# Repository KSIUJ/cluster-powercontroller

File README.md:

# cluster-powercontroller
AVR-based node power controller for the KSI computer cluster

* 32 opto-isolated channels
* Atmel ATMega328P
* USB interface via FT232R

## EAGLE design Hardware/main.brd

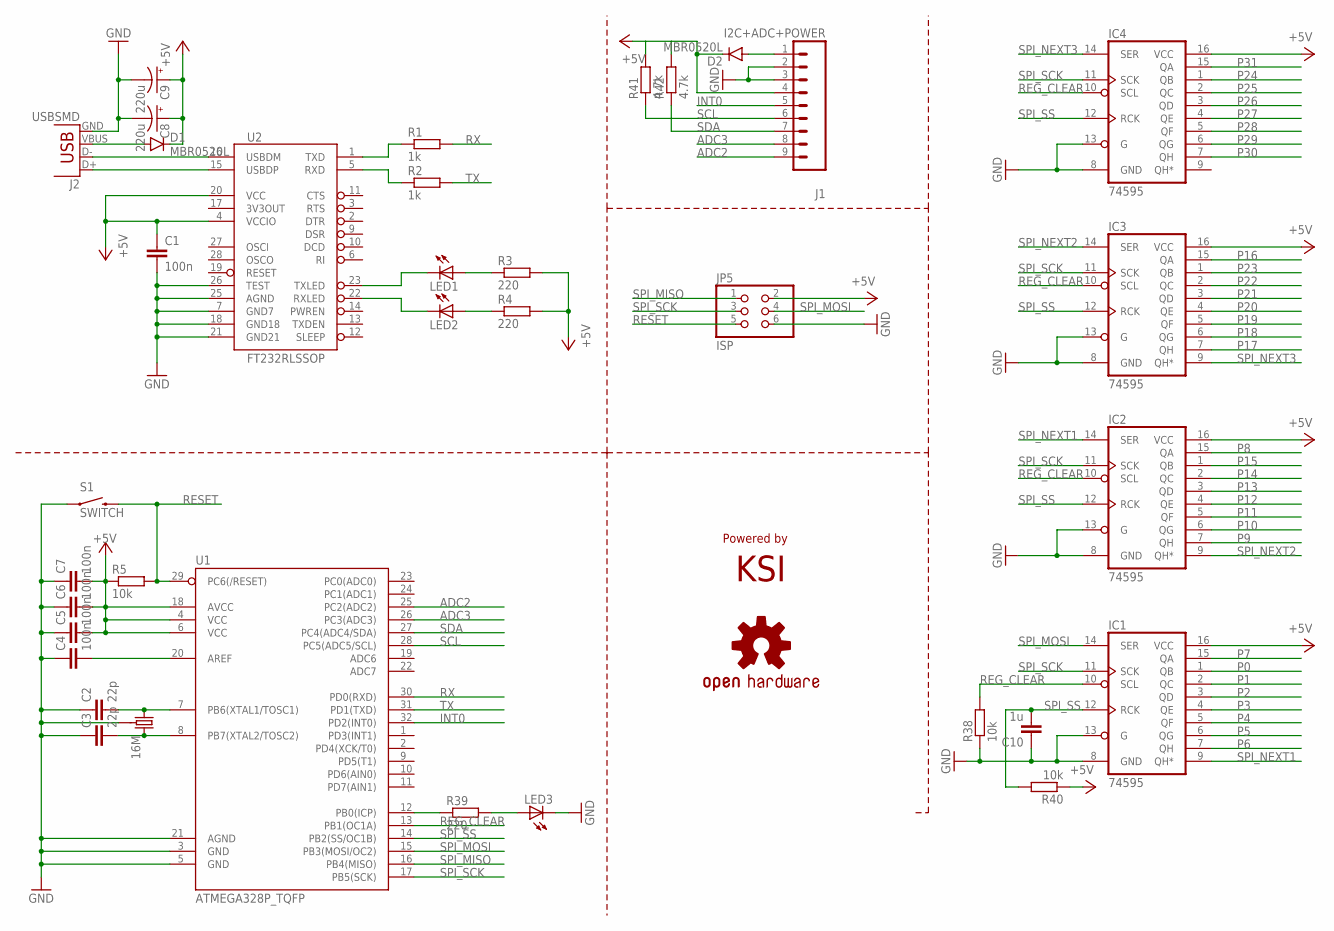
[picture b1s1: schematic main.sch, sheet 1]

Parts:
C1, C4, C5, C6, C7: 100n; C0805
C2, C3: 22p; C0805
C8, C9: 220u; EIA7343
C10: 1u; C0805
D1, D2: MBR0520L; SOD-123
IC1, IC2, IC3, IC4: 74595; TSSOP16
J1: I2C+ADC+POWER; 1X09
J2: USBSMD; USB-MINIB
JP5: ISP; 2X03
LED1, LED2, LED3: LEDSML0805; SML0805
LOGO1: OSHW-LOGOM; OSHW-LOGO-M
R1, R2: 1k; R0805
R3, R4, R39: 220; R0805
R5, R38, R40: 10k; R0805
R41, R42: 4.7k; R0805
S1: SWITCH; TACTILE_SWITCH_TALL
U1: ATMEGA328P_TQFP; TQFP32-08
U2: FT232RLSSOP; SSOP28DB
U$17: KSI; KSI_LOGO
Y2: 16M; CRYSTAL-SMD-5X3

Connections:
+5V: C1.1, C5.2, C6.2, C7.2, C8.A (+), C9.A (+), D1.C, D2.C, IC1.16 (VCC), IC2.16 (VCC), IC3.16 (VCC), IC4.16 (VCC), J1.4, JP5.2, R3.2, R4.2, R5.1, R40.1, R41.2, R42.2, U1.4 (VCC), U1.6 (VCC), U1.18 (AVCC), U2.4 (VCCIO), U2.20 (VCC); also elsewhere on the board
ADC2: J1.9, U1.25 (PC2(ADC2))
ADC3: J1.8, U1.26 (PC3(ADC3))
GND: C1.2, C2.1, C3.1, C4.1, C5.1, C6.1, C7.1, C8.C (-), C9.C (-), C10.1, IC1.8 (GND), IC1.13 (G), IC2.8 (GND), IC2.13 (G), IC3.8 (GND), IC3.13 (G), IC4.8 (GND), IC4.13 (G), J1.2, J1.3, J2.GND, JP5.6, LED3.C, R38.1, S1.A2 (1), U1.3 (GND), U1.5 (GND), U1.21 (AGND), U2.7 (GND7), U2.18 (GND18), U2.21 (GND21), U2.25 (AGND), U2.26 (TEST), Y2.2 (3), Y2.4 (3)
INT0: J1.5, U1.32 (PD2(INT0))
unnamed: J2.D-, U2.16 (USBDM)
unnamed: J2.D+, U2.15 (USBDP)
unnamed: R1.1, U2.1 (TXD)
unnamed: R2.1, U2.5 (RXD)
unnamed: LED1.A, R3.1
unnamed: LED2.A, R4.1
unnamed: LED1.C, U2.23 (TXLED)
unnamed: LED2.C, U2.22 (RXLED)
unnamed: C2.2, U1.7 (PB6(XTAL1/TOSC1)), Y2.3 (1)
unnamed: C3.2, U1.8 (PB7(XTAL2/TOSC2)), Y2.1 (2)
unnamed: C4.2, U1.20 (AREF)
unnamed: R39.1, U1.12 (PB0(ICP))
unnamed: LED3.A, R39.2
unnamed: D1.A, J2.VBUS
unnamed: D2.A, J1.1
P0: IC1.1 (QB); also elsewhere on the board
P1: IC1.2 (QC); also elsewhere on the board
P2: IC1.3 (QD); also elsewhere on the board
P3: IC1.4 (QE); also elsewhere on the board
P4: IC1.5 (QF); also elsewhere on the board
P5: IC1.6 (QG); also elsewhere on the board
P6: IC1.7 (QH); also elsewhere on the board
P7: IC1.15 (QA); also elsewhere on the board
P8: IC2.15 (QA); also elsewhere on the board
P9: IC2.7 (QH); also elsewhere on the board
P10: IC2.6 (QG); also elsewhere on the board
P11: IC2.5 (QF); also elsewhere on the board
P12: IC2.4 (QE); also elsewhere on the board
P13: IC2.3 (QD); also elsewhere on the board
P14: IC2.2 (QC); also elsewhere on the board
P15: IC2.1 (QB); also elsewhere on the board
P16: IC3.15 (QA); also elsewhere on the board
P17: IC3.7 (QH); also elsewhere on the board
P18: IC3.6 (QG); also elsewhere on the board
P19: IC3.5 (QF); also elsewhere on the board
P20: IC3.4 (QE); also elsewhere on the board
P21: IC3.3 (QD); also elsewhere on the board
P22: IC3.2 (QC); also elsewhere on the board
P23: IC3.1 (QB); also elsewhere on the board
P24: IC4.1 (QB); also elsewhere on the board
P25: IC4.2 (QC); also elsewhere on the board
P26: IC4.3 (QD); also elsewhere on the board
P27: IC4.4 (QE); also elsewhere on the board
P28: IC4.5 (QF); also elsewhere on the board
P29: IC4.6 (QG); also elsewhere on the board
P30: IC4.7 (QH); also elsewhere on the board
P31: IC4.15 (QA); also elsewhere on the board
REG_CLEAR: IC1.10 (SCL), IC2.10 (SCL), IC3.10 (SCL), IC4.10 (SCL), R38.2, U1.13 (PB1(OC1A))
RESET: JP5.5, R5.2, S1.B2 (2), U1.29 (PC6(/RESET))
RX: R1.2, U1.30 (PD0(RXD))
SCL: J1.6, R41.1, U1.28 (PC5(ADC5/SCL))
SDA: J1.7, R42.1, U1.27 (PC4(ADC4/SDA))
SPI_MISO: JP5.1, U1.16 (PB4(MISO))
SPI_MOSI: IC1.14 (SER), JP5.4, U1.15 (PB3(MOSI/OC2))
SPI_NEXT1: IC1.9 (QH*), IC2.14 (SER)
SPI_NEXT2: IC2.9 (QH*), IC3.14 (SER)
SPI_NEXT3: IC3.9 (QH*), IC4.14 (SER)
SPI_SCK: IC1.11 (SCK), IC2.11 (SCK), IC3.11 (SCK), IC4.11 (SCK), JP5.3, U1.17 (PB5(SCK))
SPI_SS: C10.2, IC1.12 (RCK), IC2.12 (RCK), IC3.12 (RCK), IC4.12 (RCK), R40.2, U1.14 (PB2(SS/OC1B))
TX: R2.2, U1.31 (PD1(TXD))

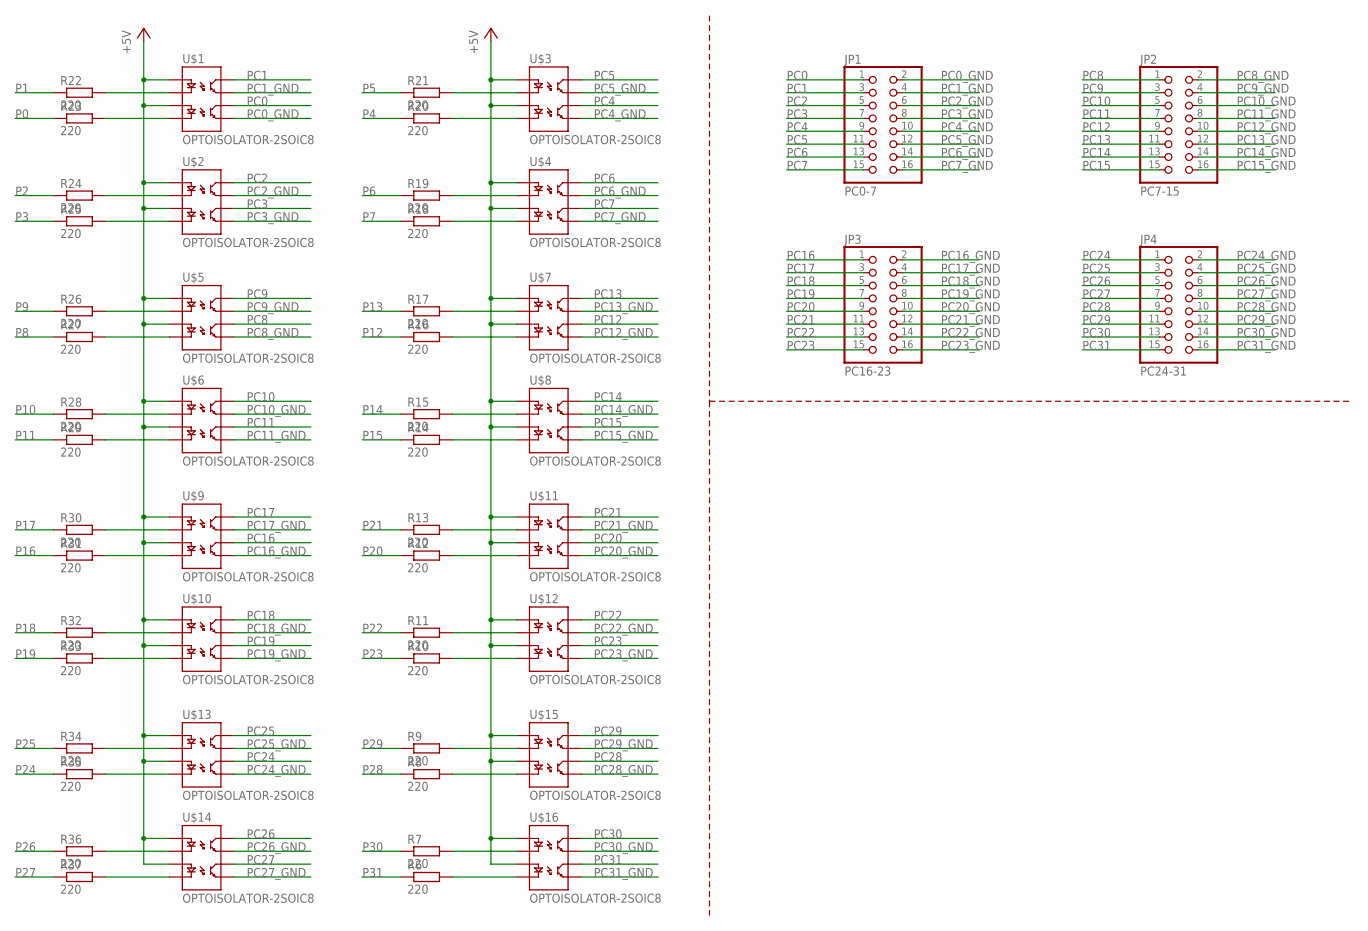
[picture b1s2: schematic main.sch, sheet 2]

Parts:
JP1: PC0-7; 2X08
JP2: PC7-15; 2X08
JP3: PC16-23; 2X08
JP4: PC24-31; 2X08
R6, R7, R8, R9, R10, R11, R12, R13, R14, R15, R16, R17, R18, R19, R20, R21, R22, R23, R24, R25, R26, R27, R28, R29, R30, R31, R32, R33, R34, R35, R36, R37: 220; R0805
U$1, U$2, U$3, U$4, U$5, U$6, U$7, U$8, U$9, U$10, U$11, U$12, U$13, U$14, U$15, U$16: OPTOISOLATOR-2SOIC8; SO08-2

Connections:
+5V: U$1.1 (A1), U$1.3 (A2), U$2.1 (A1), U$2.3 (A2), U$3.1 (A1), U$3.3 (A2), U$4.1 (A1), U$4.3 (A2), U$5.1 (A1), U$5.3 (A2), U$6.1 (A1), U$6.3 (A2), U$7.1 (A1), U$7.3 (A2), U$8.1 (A1), U$8.3 (A2), U$9.1 (A1), U$9.3 (A2), U$10.1 (A1), U$10.3 (A2), U$11.1 (A1), U$11.3 (A2), U$12.1 (A1), U$12.3 (A2), U$13.1 (A1), U$13.3 (A2), U$14.1 (A1), U$14.3 (A2), U$15.1 (A1), U$15.3 (A2), U$16.1 (A1), U$16.3 (A2); also elsewhere on the board
unnamed: R37.2, U$14.4 (C2)
unnamed: R36.2, U$14.2 (C1)
unnamed: R35.2, U$13.4 (C2)
unnamed: R34.2, U$13.2 (C1)
unnamed: R33.2, U$10.4 (C2)
unnamed: R32.2, U$10.2 (C1)
unnamed: R31.2, U$9.4 (C2)
unnamed: R30.2, U$9.2 (C1)
unnamed: R27.2, U$5.4 (C2)
unnamed: R26.2, U$5.2 (C1)
unnamed: R25.2, U$2.4 (C2)
unnamed: R24.2, U$2.2 (C1)
unnamed: R23.2, U$1.4 (C2)
unnamed: R22.2, U$1.2 (C1)
unnamed: R21.2, U$3.2 (C1)
unnamed: R20.2, U$3.4 (C2)
unnamed: R19.2, U$4.2 (C1)
unnamed: R18.2, U$4.4 (C2)
unnamed: R17.2, U$7.2 (C1)
unnamed: R16.2, U$7.4 (C2)
unnamed: R15.2, U$8.2 (C1)
unnamed: R14.2, U$8.4 (C2)
unnamed: R13.2, U$11.2 (C1)
unnamed: R12.2, U$11.4 (C2)
unnamed: R11.2, U$12.2 (C1)
unnamed: R10.2, U$12.4 (C2)
unnamed: R9.2, U$15.2 (C1)
unnamed: R8.2, U$15.4 (C2)
unnamed: R7.2, U$16.2 (C1)
unnamed: R6.2, U$16.4 (C2)
unnamed: R28.2, U$6.2 (C1)
unnamed: R29.2, U$6.4 (C2)
P0: R23.1; also elsewhere on the board
P1: R22.1; also elsewhere on the board
P2: R24.1; also elsewhere on the board
P3: R25.1; also elsewhere on the board
P4: R20.1; also elsewhere on the board
P5: R21.1; also elsewhere on the board
P6: R19.1; also elsewhere on the board
P7: R18.1; also elsewhere on the board
P8: R27.1; also elsewhere on the board
P9: R26.1; also elsewhere on the board
P10: R28.1; also elsewhere on the board
P11: R29.1; also elsewhere on the board
P12: R16.1; also elsewhere on the board
P13: R17.1; also elsewhere on the board
P14: R15.1; also elsewhere on the board
P15: R14.1; also elsewhere on the board
P16: R31.1; also elsewhere on the board
P17: R30.1; also elsewhere on the board
P18: R32.1; also elsewhere on the board
P19: R33.1; also elsewhere on the board
P20: R12.1; also elsewhere on the board
P21: R13.1; also elsewhere on the board
P22: R11.1; also elsewhere on the board
P23: R10.1; also elsewhere on the board
P24: R35.1; also elsewhere on the board
P25: R34.1; also elsewhere on the board
P26: R36.1; also elsewhere on the board
P27: R37.1; also elsewhere on the board
P28: R8.1; also elsewhere on the board
P29: R9.1; also elsewhere on the board
P30: R7.1; also elsewhere on the board
P31: R6.1; also elsewhere on the board
PC0: JP1.1, U$1.6 (CL2)
PC0_GND: JP1.2, U$1.5 (EM2)
PC1: JP1.3, U$1.8 (CL1)
PC1_GND: JP1.4, U$1.7 (EM1)
PC2: JP1.5, U$2.8 (CL1)
PC2_GND: JP1.6, U$2.7 (EM1)
PC3: JP1.7, U$2.6 (CL2)
PC3_GND: JP1.8, U$2.5 (EM2)
PC4: JP1.9, U$3.6 (CL2)
PC4_GND: JP1.10, U$3.5 (EM2)
PC5: JP1.11, U$3.8 (CL1)
PC5_GND: JP1.12, U$3.7 (EM1)
PC6: JP1.13, U$4.8 (CL1)
PC6_GND: JP1.14, U$4.7 (EM1)
PC7: JP1.15, U$4.6 (CL2)
PC7_GND: JP1.16, U$4.5 (EM2)
PC8: JP2.1, U$5.6 (CL2)
PC8_GND: JP2.2, U$5.5 (EM2)
PC9: JP2.3, U$5.8 (CL1)
PC9_GND: JP2.4, U$5.7 (EM1)
PC10: JP2.5, U$6.8 (CL1)
PC10_GND: JP2.6, U$6.7 (EM1)
PC11: JP2.7, U$6.6 (CL2)
PC11_GND: JP2.8, U$6.5 (EM2)
PC12: JP2.9, U$7.6 (CL2)
PC12_GND: JP2.10, U$7.5 (EM2)
PC13: JP2.11, U$7.8 (CL1)
PC13_GND: JP2.12, U$7.7 (EM1)
PC14: JP2.13, U$8.8 (CL1)
PC14_GND: JP2.14, U$8.7 (EM1)
PC15: JP2.15, U$8.6 (CL2)
PC15_GND: JP2.16, U$8.5 (EM2)
PC16: JP3.1, U$9.6 (CL2)
PC16_GND: JP3.2, U$9.5 (EM2)
PC17: JP3.3, U$9.8 (CL1)
PC17_GND: JP3.4, U$9.7 (EM1)
PC18: JP3.5, U$10.8 (CL1)
PC18_GND: JP3.6, U$10.7 (EM1)
PC19: JP3.7, U$10.6 (CL2)
PC19_GND: JP3.8, U$10.5 (EM2)
PC20: JP3.9, U$11.6 (CL2)
PC20_GND: JP3.10, U$11.5 (EM2)
PC21: JP3.11, U$11.8 (CL1)
PC21_GND: JP3.12, U$11.7 (EM1)
PC22: JP3.13, U$12.8 (CL1)
PC22_GND: JP3.14, U$12.7 (EM1)
PC23: JP3.15, U$12.6 (CL2)
PC23_GND: JP3.16, U$12.5 (EM2)
PC24: JP4.1, U$13.6 (CL2)
PC24_GND: JP4.2, U$13.5 (EM2)
PC25: JP4.3, U$13.8 (CL1)
PC25_GND: JP4.4, U$13.7 (EM1)
PC26: JP4.5, U$14.8 (CL1)
PC26_GND: JP4.6, U$14.7 (EM1)
PC27: JP4.7, U$14.6 (CL2)
PC27_GND: JP4.8, U$14.5 (EM2)
PC28: JP4.9, U$15.6 (CL2)
PC28_GND: JP4.10, U$15.5 (EM2)
PC29: JP4.11, U$15.8 (CL1)
PC29_GND: JP4.12, U$15.7 (EM1)
PC30: JP4.13, U$16.8 (CL1)
PC30_GND: JP4.14, U$16.7 (EM1)
PC31: JP4.15, U$16.6 (CL2)
PC31_GND: JP4.16, U$16.5 (EM2)

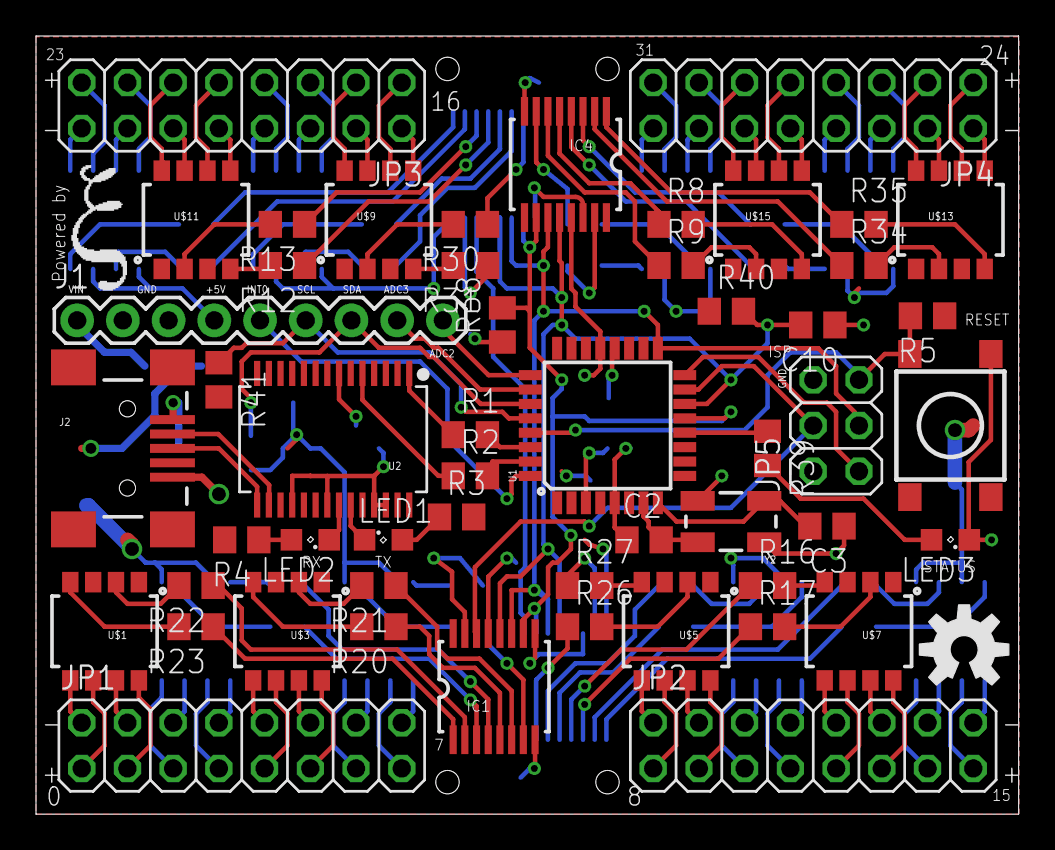
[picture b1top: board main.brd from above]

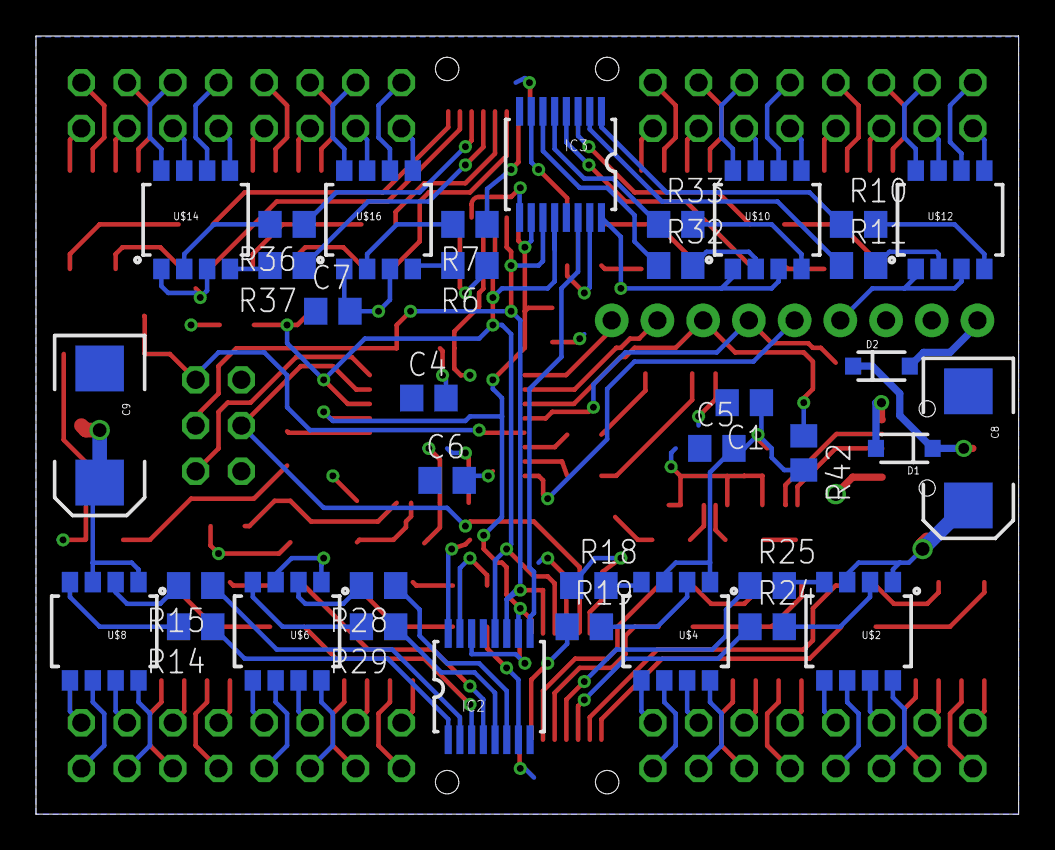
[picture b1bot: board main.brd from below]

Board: 2 copper layers, 54.6 x 43.2 mm, 90 parts (36 on the bottom side), 161 nets.

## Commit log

2017-01-04 Add hardware design files
2017-01-07 Add pin descriptions on pcb, optimize +5V polygon
2017-03-03 Add AtmelStudio project
2017-03-03 Add USART
2017-03-25 Add simple shift-reg function
2017-03-25 Move shift register code to separate unit
2017-03-27 Add time counter
2017-03-27 Add command interpreter
2017-03-27 Add watchdog
    (untested)
2017-03-27 Add Controller class and power on/off commands
2017-03-27 Add checksums, Minor code cleanup
    (untested)
2017-03-27 Add communication protocol documentation
2017-03-27 Fix error code 15 convention mismatch
2017-03-28 Fix port mapping
2017-05-17 Change checksum to XOR, fix bug in controller
2017-05-17 Fix reset source detection

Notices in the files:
parts and their libraries:
SparkFun-DigitalIC: Licensing: Creative Commons ShareAlike 4.0 International - https://creativecommons.org/licenses/by-sa/4.0
